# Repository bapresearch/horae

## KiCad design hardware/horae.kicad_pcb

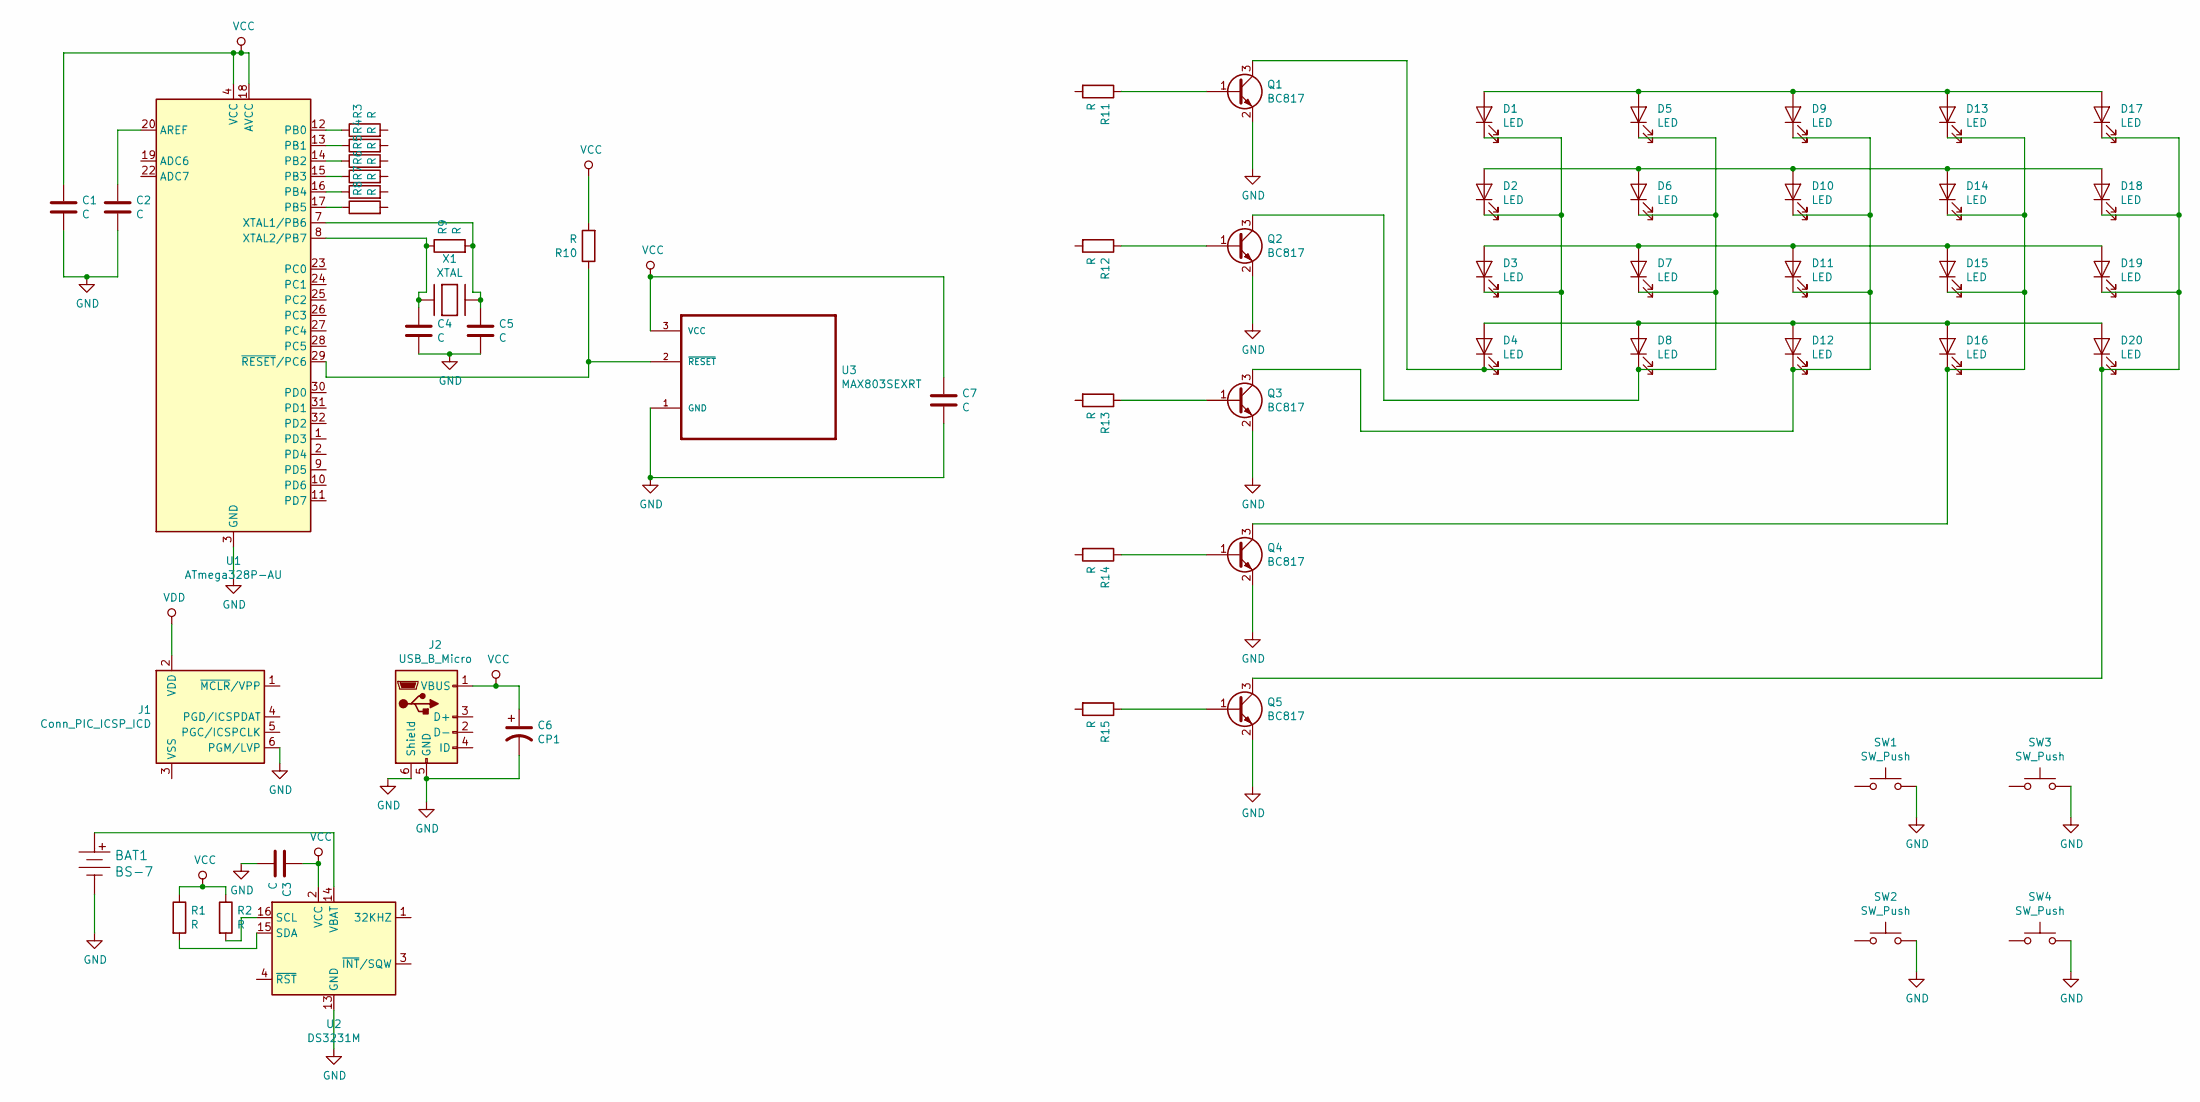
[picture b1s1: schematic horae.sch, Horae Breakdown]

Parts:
BAT1: BS-7; Battery_Holder_Coin_2032_BS-7; MPN BS-7; Digi-Key_PN BS-7-ND
C1, C2, C3, C4, C5, C7: C; C_0201_0603Metric
C6: CP1; CP_Elec_3x5.3
D1, D2, D3, D4, D5, D6, D7, D8, D9, D10, D11, D12, D13, D14, D15, D16, D17, D18, D19, D20: LED; LED-APA102-2020
J1: Conn_PIC_ICSP_ICD; PinHeader_1x06_P2.54mm_Horizontal
J2: USB_B_Micro; USB_Micro-B_Amphenol_10103594-0001LF_Horizontal
Q1, Q2, Q3, Q4, Q5: BC817; SOT-23
R1, R2, R3, R4, R5, R6, R7, R8, R9, R10, R11, R12, R13, R14, R15: R; R_0201_0603Metric
SW1, SW2, SW3, SW4: SW_Push; SW_Push_1P1T-SH_NO_CK_KMR2xxG
U1: ATmega328P-AU; TQFP-32_7x7mm_P0.8mm
U2: DS3231M; SOIC-16W_7.5x10.3mm_P1.27mm
U3: MAX803SEXRT; SOT65P210X110-3N
X1: XTAL; XTAL3215

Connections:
GND: BAT1.Neg, C1.2, C2.2, C3.2, C4.2, C5.2, C6.2, C7.2, J1.6 (PGM/LVP), J2.5 (GND), J2.6 (Shield), Q1.2 (E), Q2.2 (E), Q3.2 (E), Q4.2 (E), Q5.2 (E), SW1.2, SW2.2, SW3.2, SW4.2, U1.3 (GND), U1.5 (GND), U1.21 (GND), U2.5 (GND), U2.6 (GND), U2.7 (GND), U2.8 (GND), U2.9 (GND), U2.10 (GND), U2.11 (GND), U2.12 (GND), U2.13 (GND), U3.1 (GND)
unnamed: BAT1.Pos, U2.14 (VBAT)
unnamed: C2.1, U1.20 (AREF)
unnamed: C4.1, R9.1, U1.8 (XTAL2/PB7), X1.P$1
unnamed: C5.1, R9.2, U1.7 (XTAL1/PB6), X1.P$2
unnamed: D1.1 (K), D2.1 (K), D3.1 (K), D4.1 (K), Q1.3 (C)
unnamed: D1.2 (A), D5.2 (A), D9.2 (A), D13.2 (A), D17.2 (A)
unnamed: D5.1 (K), D6.1 (K), D7.1 (K), D8.1 (K), Q2.3 (C)
unnamed: D9.1 (K), D10.1 (K), D11.1 (K), D12.1 (K), Q3.3 (C)
unnamed: D2.2 (A), D6.2 (A), D10.2 (A), D14.2 (A), D18.2 (A)
unnamed: D3.2 (A), D7.2 (A), D11.2 (A), D15.2 (A), D19.2 (A)
unnamed: D4.2 (A), D8.2 (A), D12.2 (A), D16.2 (A), D20.2 (A)
unnamed: D13.1 (K), D14.1 (K), D15.1 (K), D16.1 (K), Q4.3 (C)
unnamed: D17.1 (K), D18.1 (K), D19.1 (K), D20.1 (K), Q5.3 (C)
unnamed: Q1.1 (B), R11.1
unnamed: Q2.1 (B), R12.1
unnamed: Q3.1 (B), R13.1
unnamed: Q4.1 (B), R14.1
unnamed: Q5.1 (B), R15.1
unnamed: R1.2, U2.15 (SDA)
unnamed: R2.2, U2.16 (SCL)
unnamed: R3.1, U1.12 (PB0)
unnamed: R4.1, U1.13 (PB1)
unnamed: R5.1, U1.14 (PB2)
unnamed: R6.1, U1.15 (PB3)
unnamed: R7.1, U1.16 (PB4)
unnamed: R8.1, U1.17 (PB5)
unnamed: R10.1, U1.29 (~RESET~/PC6), U3.2 (~RESET~)
VCC: C1.1, C3.1, C6.1, C7.1, J2.1 (VBUS), R1.1, R2.1, R10.2, U1.4 (VCC), U1.6 (VCC), U1.18 (AVCC), U2.2 (VCC), U3.3 (VCC)
VDD: J1.2 (VDD)

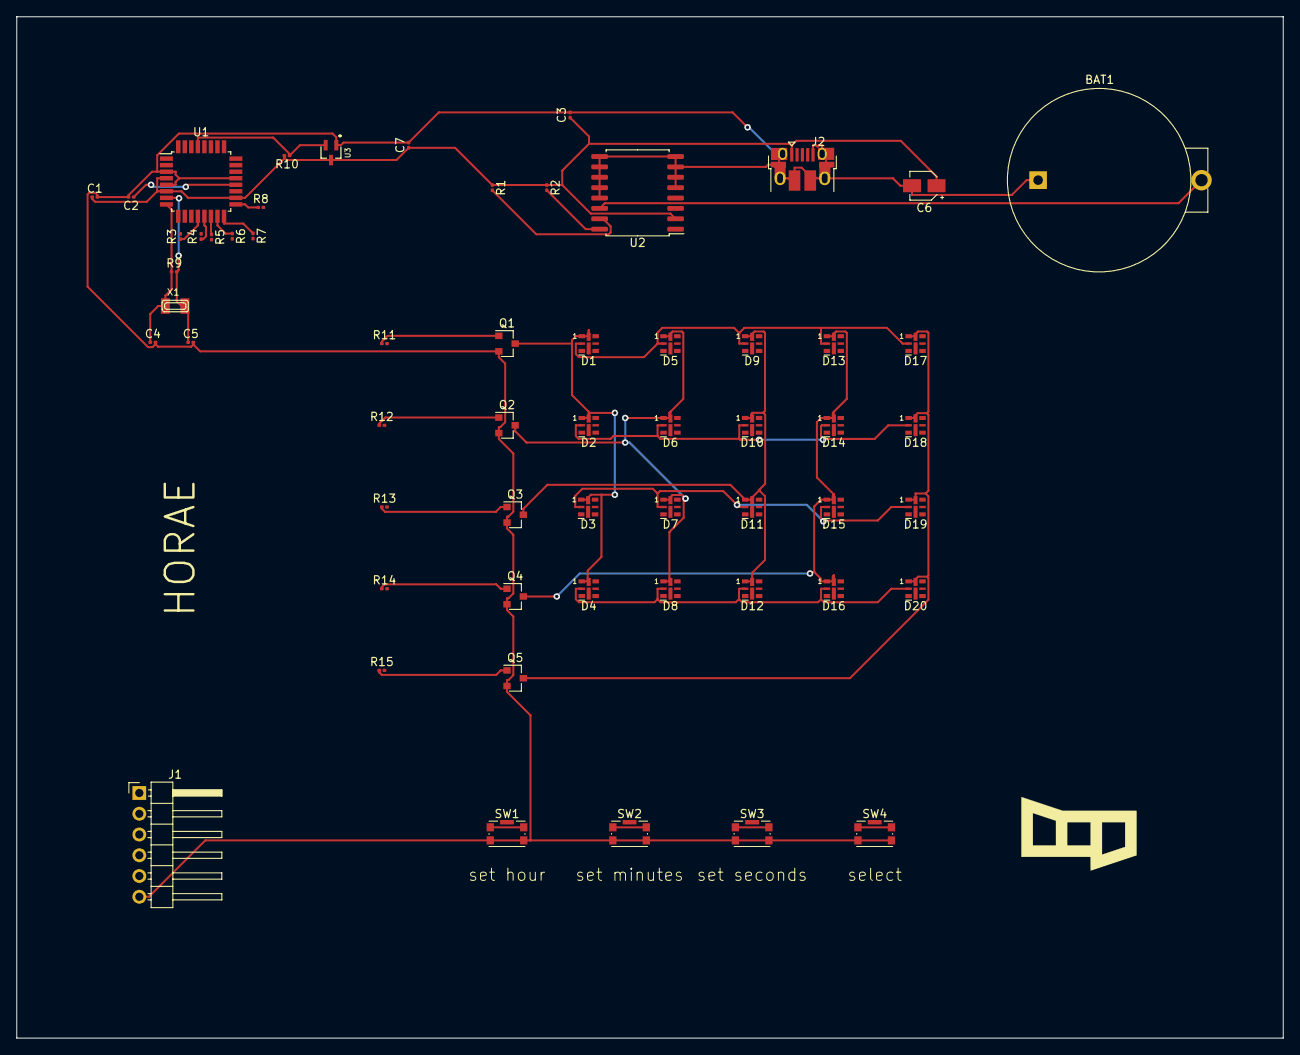
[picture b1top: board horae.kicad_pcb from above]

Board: 2 copper layers, 155.0 x 125.0 mm, 58 parts (0 on the bottom side), 29 nets.

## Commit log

2020-05-09 finish pcb and add horae.c
